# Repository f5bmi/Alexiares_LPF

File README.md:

# Alexiares_LPF
This repository contains the Low Pass Filter project of the OpenHPSDR Alexiares frontend

This work is protected by the TAPR Open Hardware Licence https://www.tapr.org/ohl.html

Original work by Graham Haddock, KE9H and Phil Harman, VK6APH.

Board's dimensions are oversized to fit 10cmx10cm size.

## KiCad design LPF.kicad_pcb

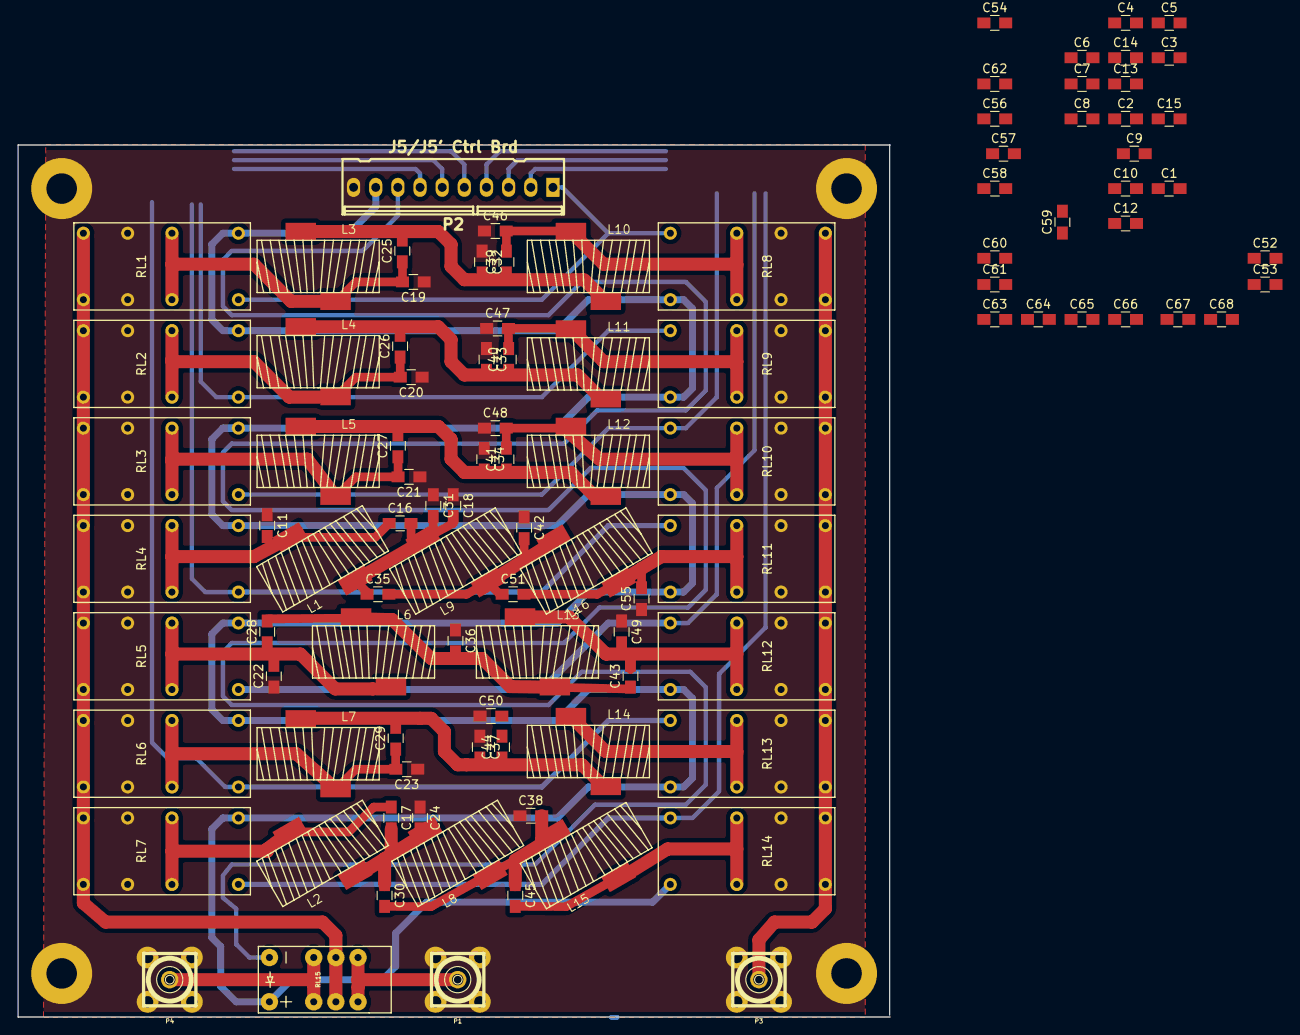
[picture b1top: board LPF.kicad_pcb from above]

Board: 4 copper layers, 100.0 x 100.0 mm, 107 parts (0 on the bottom side), 37 nets.

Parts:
 : MountingHole_3.5mm_Pad
 #2,  #3,  #4: MountingHole_3.5mm_Pad
C1, C2, C3, C4, C5, C6, C7, C8, C9, C10, C12, C13, C14, C15, C52, C53, C54, C56, C57, C58, C59, C60, C61, C62, C63, C64, C65, C66, C67: 10n; C_0805_HandSoldering
C11, C16, C17, C18, C19, C20, C21, C22, C23, C24, C25, C26, C27, C28, C29, C30, C31, C32, C33, C34, C35, C36, C37, C38, C39, C40, C41, C42, C43, C44, C45, C46, C47, C48, C49, C50, C51, C55: C; C_0805_HandSoldering
C68: 100n; C_0805_HandSoldering
L1, L2, L3, L4, L5, L6, L7, L8, L9, L10, L11, L12, L13, L14, L15, L16: L; T50_V_smd
P1, P3, P4: SMA; SMA_PINS
P2: J5/J5' Ctrl Brd; kk100_22-23-2101
RL1, RL2, RL3, RL4, RL5, RL6, RL7, RL8, RL9, RL10, RL11, RL12, RL13, RL14: D2nxx; D2n12DC
RL15: EC2-12NU; THT_2_formC

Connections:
6m_Bypass: C15.1, C59.2, P2.7, RL7.16, RL14.16
12/10m: C14.1, C58.2, P2.6, RL6.16, RL13.16
17/15m: C13.1, C57.2, P2.5, RL5.16, RL12.16
30/20m: C12.1, C56.2, P2.4, RL4.16, RL11.16
40m: C10.1, C54.2, P2.3, RL3.16, RL10.16
80m: C9.1, C53.2, P2.2, RL2.16, RL9.16
160m: C8.1, C52.2, P2.1, RL1.16, RL8.16
+12V: C1.1, C2.1, C3.1, C4.1, C5.1, C6.1, C7.1, C60.1, C61.1, C62.1, C63.1, C64.1, C65.1, C66.1, C67.1, C68.1, P2.9, RL1.1, RL2.1, RL3.1, RL4.1, RL5.1, RL6.1, RL7.1, RL8.1, RL9.1, RL10.1, RL11.1, RL12.1, RL13.1, RL14.1, RL15.1
GND: .1, #2.1, #3.1, #4.1, C1.2, C2.2, C3.2, C4.2, C5.2, C6.2, C7.2, C8.2, C9.2, C10.2, C11.1, C12.2, C13.2, C14.2, C15.2, C18.1, C19.1, C20.1, C21.1, C22.1, C23.1, C24.1, C31.1, C32.1, C33.1, C34.1, C36.1, C37.1, C38.1, C42.1, C46.1, C47.1, C48.1, C49.1, C50.1, C52.1, C53.1, C54.1, C55.1, C56.1, C57.1, C58.1, C59.1, C60.2, C61.2, C62.2, C63.2, C64.2, C65.2, C66.2, C67.2, C68.2, P1.2, P2.10, P3.2, P4.2, RL1.6, RL1.11, RL2.6, RL2.11, RL3.6, RL3.11, RL4.6, RL4.11, RL5.6, RL5.11, RL6.6, RL6.11, RL7.6, RL7.11, RL8.6, RL8.11, RL9.6, RL9.11, RL10.6, RL10.11, RL11.6, RL11.11, RL12.6, RL12.11, RL13.6, RL13.11, RL14.6, RL14.11
unnamed: C11.2, C16.1, L1.1, RL4.4, RL4.13
unnamed: C16.2, C18.2, C31.2, C35.1, L1.2, L9.1
unnamed: C17.1, L2.1, RL7.4, RL7.13
unnamed: C17.2, C24.2, C30.1, L2.2, L8.1
unnamed: C19.2, C25.1, L3.1, RL1.4, RL1.13
unnamed: C20.2, C26.1, L4.1, RL2.4, RL2.13
unnamed: C21.2, C27.1, L5.1, RL3.4, RL3.13
unnamed: C22.2, C28.1, L6.1, RL5.4, RL5.13
unnamed: C23.2, C29.1, L7.1, RL6.4, RL6.13
unnamed: C25.2, C32.2, C39.1, L3.2, L10.1
unnamed: C26.2, C33.2, C40.1, L4.2, L11.1
unnamed: C27.2, C34.2, C41.1, L5.2, L12.1
unnamed: C28.2, C36.2, C43.1, L6.2, L13.1
unnamed: C29.2, C37.2, C44.1, L7.2, L14.1
unnamed: C30.2, C38.2, C45.1, L8.2, L15.1
unnamed: C35.2, C42.2, C51.1, L9.2, L16.1
unnamed: C39.2, C46.2, L10.2, RL8.4, RL8.13
unnamed: C40.2, C47.2, L11.2, RL9.4, RL9.13
unnamed: C41.2, C48.2, L12.2, RL10.4, RL10.13
unnamed: C43.2, C49.2, L13.2, RL12.4, RL12.13
unnamed: C44.2, C50.2, L14.2, RL13.4, RL13.13
unnamed: C45.2, L15.2, RL14.4, RL14.13
unnamed: C51.2, C55.2, L16.2, RL11.4, RL11.13
unnamed: P1.1, RL15.5, RL15.8
unnamed: P3.1, RL8.8, RL8.9, RL9.8, RL9.9, RL10.8, RL10.9, RL11.8, RL11.9, RL12.8, RL12.9, RL13.8, RL13.9, RL14.8, RL14.9
unnamed: P4.1, RL15.3, RL15.10
unnamed: RL1.8, RL1.9, RL2.8, RL2.9, RL3.8, RL3.9, RL4.8, RL4.9, RL5.8, RL5.9, RL6.8, RL6.9, RL7.8, RL7.9, RL15.4, RL15.9
TX_RX_RLY: P2.8, RL15.12

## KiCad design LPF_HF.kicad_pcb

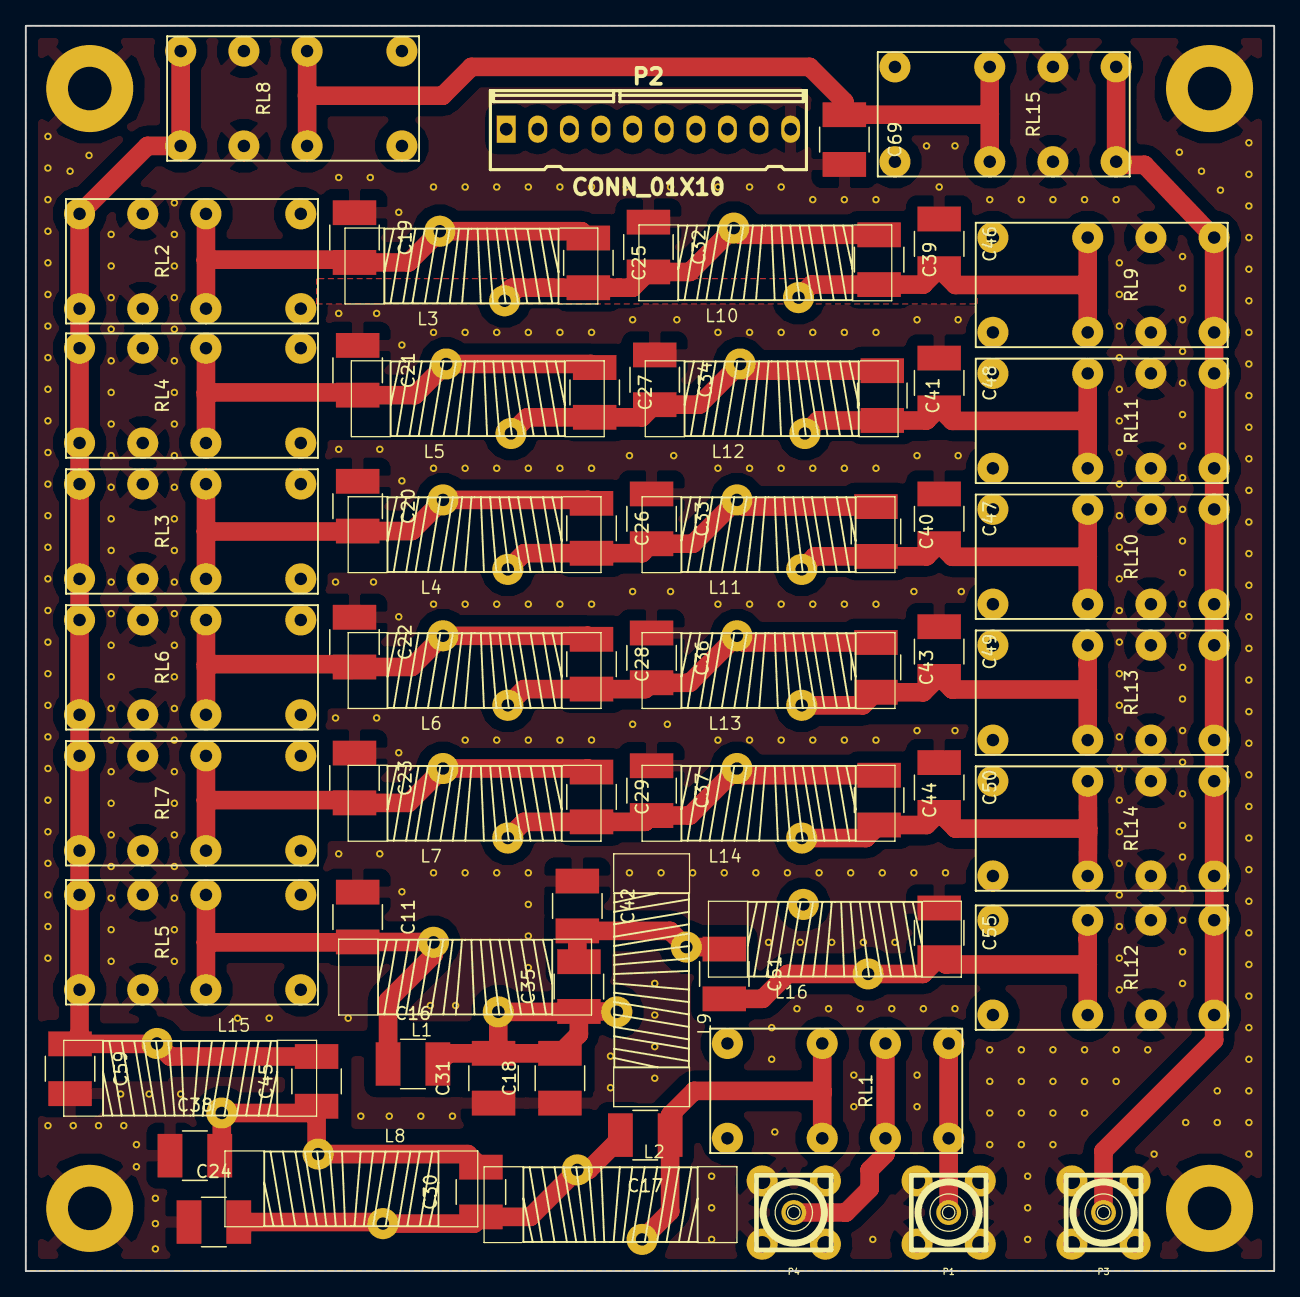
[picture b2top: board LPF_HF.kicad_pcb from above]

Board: 2 copper layers, 100.3 x 100.1 mm, 79 parts (0 on the bottom side), 29 nets.

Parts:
C11, C16, C18, C19, C20, C21, C22, C23, C25, C26, C27, C28, C29, C31, C32, C33, C34, C35, C36, C37, C39, C40, C41, C42, C43, C44, C46, C47, C48, C49, C50, C51, C55, C69: C; ATC_500_HandSoldering
C17, C59: 24p; ATC_500_HandSoldering
C24: 31p; ATC_500_HandSoldering
C30: 15p; ATC_500_HandSoldering
C38: 68p; ATC_500_HandSoldering
C45: 4.7; ATC_500_HandSoldering
L1, L2, L3, L4, L5, L6, L7, L8, L9, L10, L11, L12, L13, L14, L15, L16: L; T50_T68
P1, P3, P4: SMA; SMA_PINS
P2: CONN_01X10; kk100_22-23-2101
RL1, RL2, RL3, RL4, RL5, RL6, RL7, RL8, RL9, RL10, RL11, RL12, RL13, RL14, RL15: D2n
TP1, TP2, TP3, TP4: TEST; MountingHole_3.5mm_Pad

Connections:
+12V: P2.9, RL1.16, RL2.16, RL3.16, RL4.1, RL5.1, RL6.1, RL7.16, RL8.16, RL9.1, RL10.1, RL11.16, RL12.16, RL13.16, RL14.1, RL15.1
GND: C11.1, C18.1, C19.1, C20.1, C21.1, C22.1, C23.1, C24.1, C31.1, C32.1, C33.1, C34.1, C36.1, C37.1, C38.1, C42.1, C46.1, C47.1, C48.1, C49.1, C50.1, C55.1, C59.2, C69.2, P1.2, P2.10, P3.2, P4.2, RL2.6, RL2.11, RL3.6, RL3.11, RL4.6, RL4.11, RL5.6, RL5.11, RL6.6, RL6.11, RL7.6, RL7.11, RL8.6, RL8.11, RL9.6, RL9.11, RL10.6, RL10.11, RL11.6, RL11.11, RL12.6, RL12.11, RL13.6, RL13.11, RL14.6, RL14.11, RL15.6, RL15.11, TP1.1, TP2.1, TP3.1, TP4.1
unnamed: C11.2, C16.1, L1.1, RL5.4, RL5.13
unnamed: C16.2, C18.2, C31.2, C35.1, L1.2, L9.1
unnamed: C17.1, L2.1, RL1.4, RL1.13
unnamed: C17.2, C24.2, C30.1, L2.2, L8.1
unnamed: C19.2, C25.1, L3.1, RL2.4, RL2.13
unnamed: C20.2, C26.1, L4.1, RL3.4, RL3.13
unnamed: C21.2, C27.1, L5.1, RL4.4, RL4.13
unnamed: C22.2, C28.1, L6.1, RL6.4, RL6.13
unnamed: C23.2, C29.1, L7.1, RL7.4, RL7.13
unnamed: C25.2, C32.2, C39.1, L3.2, L10.1
unnamed: C26.2, C33.2, C40.1, L4.2, L11.1
unnamed: C27.2, C34.2, C41.1, L5.2, L12.1
unnamed: C28.2, C36.2, C43.1, L6.2, L13.1
unnamed: C29.2, C37.2, C44.1, L7.2, L14.1
unnamed: C30.2, C38.2, C45.1, L8.2, L15.1
unnamed: C35.2, C42.2, C51.1, L9.2, L16.1
unnamed: C39.2, C46.2, L10.2, RL9.4, RL9.13
unnamed: C40.2, C47.2, L11.2, RL10.4, RL10.13
unnamed: C41.2, C48.2, L12.2, RL11.4, RL11.13
unnamed: C43.2, C49.2, L13.2, RL13.4, RL13.13
unnamed: C44.2, C50.2, L14.2, RL14.4, RL14.13
unnamed: C45.2, C59.1, L15.2, RL2.8, RL2.9, RL3.8, RL3.9, RL4.8, RL4.9, RL5.8, RL5.9, RL6.8, RL6.9, RL7.8, RL7.9, RL8.8, RL8.9
unnamed: C51.2, C55.2, L16.2, RL12.4, RL12.13
unnamed: C69.1, RL8.4, RL8.13, RL15.4, RL15.13
unnamed: P1.1, RL1.8, RL1.9
unnamed: P3.1, RL9.8, RL9.9, RL10.8, RL10.9, RL11.8, RL11.9, RL12.8, RL12.9, RL13.8, RL13.9, RL14.8, RL14.9, RL15.8, RL15.9
unnamed: P4.1, RL1.6, RL1.11

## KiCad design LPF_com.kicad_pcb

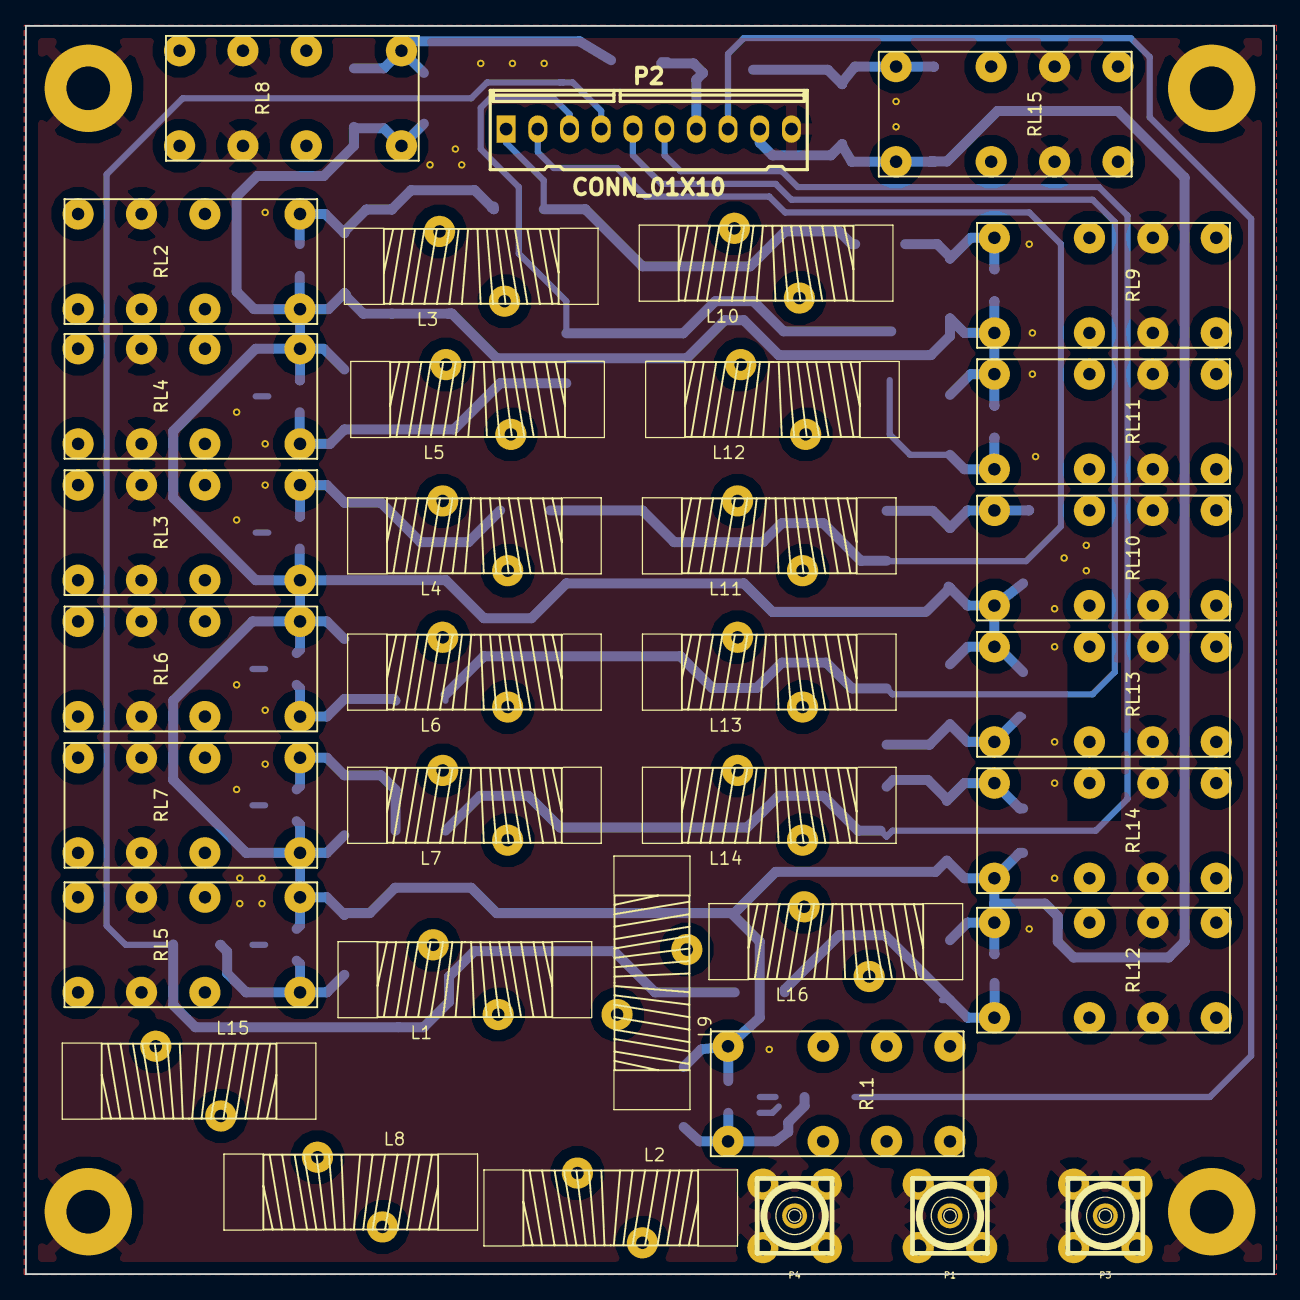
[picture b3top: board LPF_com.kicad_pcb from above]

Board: 2 copper layers, 100.0 x 100.0 mm, 99 parts (0 on the bottom side), 52 nets.

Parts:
C1, C2, C3, C4, C5, C6, C7, C8, C9, C10, C12, C13, C14, C15, C52, C53, C54, C56, C57, C58, C60, C61, C62, C63, C64, C65, C66, C70, C71: 10n; C_0805_HandSoldering
C68: 100n; C_0805_HandSoldering
D1, D2, D3, D4, D5, D6, D7, D8, D9, D10, D11, D12, D13, D14, D15: D_ALT; D_MELF
L1, L2, L3, L4, L5, L6, L7, L8, L9, L10, L11, L12, L13, L14, L15, L16: L; T50_T68
L17, L18, L19, L20, L21, L22, L23, L24, L25, L26, L27, L28, L29, L30, L31: choke; L_1210_HandSoldering
P1, P3, P4: SMA; SMA_PINS
P2: CONN_01X10; kk100_22-23-2101
RL1, RL2, RL3, RL4, RL5, RL6, RL7, RL8, RL9, RL10, RL11, RL12, RL13, RL14, RL15: D2n
TP1, TP2, TP3, TP4: TEST; MountingHole_3.5mm_Pad

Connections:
6m_Bypass: L17.1, L18.1, P2.7
12/10m: L22.1, L26.1, P2.6
17/15m: L21.2, L27.2, P2.5
30/20m: L19.2, L20.2, P2.4
40m: L25.2, L30.2, P2.3
80m: L24.2, L29.1, P2.2
160m: L23.1, L28.1, P2.1
+12V: C3.1, C4.1, C5.1, C7.1, C8.1, C9.1, C14.1, C54.2, C56.2, C57.2, C60.1, C61.1, C65.1, C66.1, C71.1, D1.1, D2.1, D3.1, D4.1, D5.1, D6.1, D7.1, D8.1, D9.1, D10.1, D11.1, D12.1, D13.1, D14.1, D15.1, P2.9, RL1.16, RL2.16, RL3.16, RL4.1, RL5.1, RL6.1, RL7.16, RL8.16, RL9.1, RL10.1, RL11.16, RL12.16, RL13.16, RL14.1, RL15.1
GND: C1.2, C2.2, C3.2, C4.2, C5.2, C6.2, C7.2, C8.2, C9.2, C10.2, C12.2, C13.2, C14.2, C15.2, C52.1, C53.1, C54.1, C56.1, C57.1, C58.1, C60.2, C61.2, C62.2, C63.2, C64.2, C65.2, C66.2, C68.2, C70.1, C71.2, P1.2, P2.10, P3.2, P4.2, RL2.6, RL2.11, RL3.6, RL3.11, RL4.6, RL4.11, RL5.6, RL5.11, RL6.6, RL6.11, RL7.6, RL7.11, RL8.6, RL8.11, RL9.6, RL9.11, RL10.6, RL10.11, RL11.6, RL11.11, RL12.6, RL12.11, RL13.6, RL13.11, RL14.6, RL14.11, RL15.6, RL15.11, TP1.1, TP2.1, TP3.1, TP4.1
unnamed: C1.1, D1.2, L23.2, RL2.1
unnamed: C2.1, D2.2, L24.1, RL3.1
unnamed: C6.1, D6.2, L22.2, RL7.1
unnamed: C10.1, D3.2, L25.1, RL4.16
unnamed: L1.1, RL5.4, RL5.13
unnamed: C12.1, D4.2, L19.1, RL5.16
unnamed: C13.1, D5.2, L21.1, RL6.16
unnamed: C15.1, D7.2, L18.2, RL8.1
unnamed: L1.2, L9.1
unnamed: L2.1, RL1.4, RL1.13
unnamed: L2.2, L8.1
unnamed: L3.1, RL2.4, RL2.13
unnamed: L4.1, RL3.4, RL3.13
unnamed: L5.1, RL4.4, RL4.13
unnamed: L6.1, RL6.4, RL6.13
unnamed: L7.1, RL7.4, RL7.13
unnamed: L3.2, L10.1
unnamed: L4.2, L11.1
unnamed: L5.2, L12.1
unnamed: L6.2, L13.1
unnamed: L7.2, L14.1
unnamed: L8.2, L15.1
unnamed: L9.2, L16.1
unnamed: L10.2, RL9.4, RL9.13
unnamed: L11.2, RL10.4, RL10.13
unnamed: L12.2, RL11.4, RL11.13
unnamed: L13.2, RL13.4, RL13.13
unnamed: L14.2, RL14.4, RL14.13
unnamed: L15.2, RL2.8, RL2.9, RL3.8, RL3.9, RL4.8, RL4.9, RL5.8, RL5.9, RL6.8, RL6.9, RL7.8, RL7.9, RL8.8, RL8.9
unnamed: L16.2, RL12.4, RL12.13
unnamed: C52.2, D8.2, L28.2, RL9.16
unnamed: C53.2, D9.2, L29.2, RL10.16
unnamed: C58.2, D13.2, L26.2, RL14.16
unnamed: C62.1, D10.2, L30.1, RL11.1
unnamed: C63.1, D11.2, L20.1, RL12.1
unnamed: C64.1, D12.2, L27.1, RL13.1
unnamed: C68.1, D15.2, L31.2, RL1.1
unnamed: RL8.4, RL8.13, RL15.4, RL15.13
unnamed: C70.2, D14.2, L17.2, RL15.16
unnamed: P1.1, RL1.8, RL1.9
unnamed: P3.1, RL9.8, RL9.9, RL10.8, RL10.9, RL11.8, RL11.9, RL12.8, RL12.9, RL13.8, RL13.9, RL14.8, RL14.9, RL15.8, RL15.9
unnamed: P4.1, RL1.6, RL1.11
TX_RX_RLY: L31.1, P2.8
